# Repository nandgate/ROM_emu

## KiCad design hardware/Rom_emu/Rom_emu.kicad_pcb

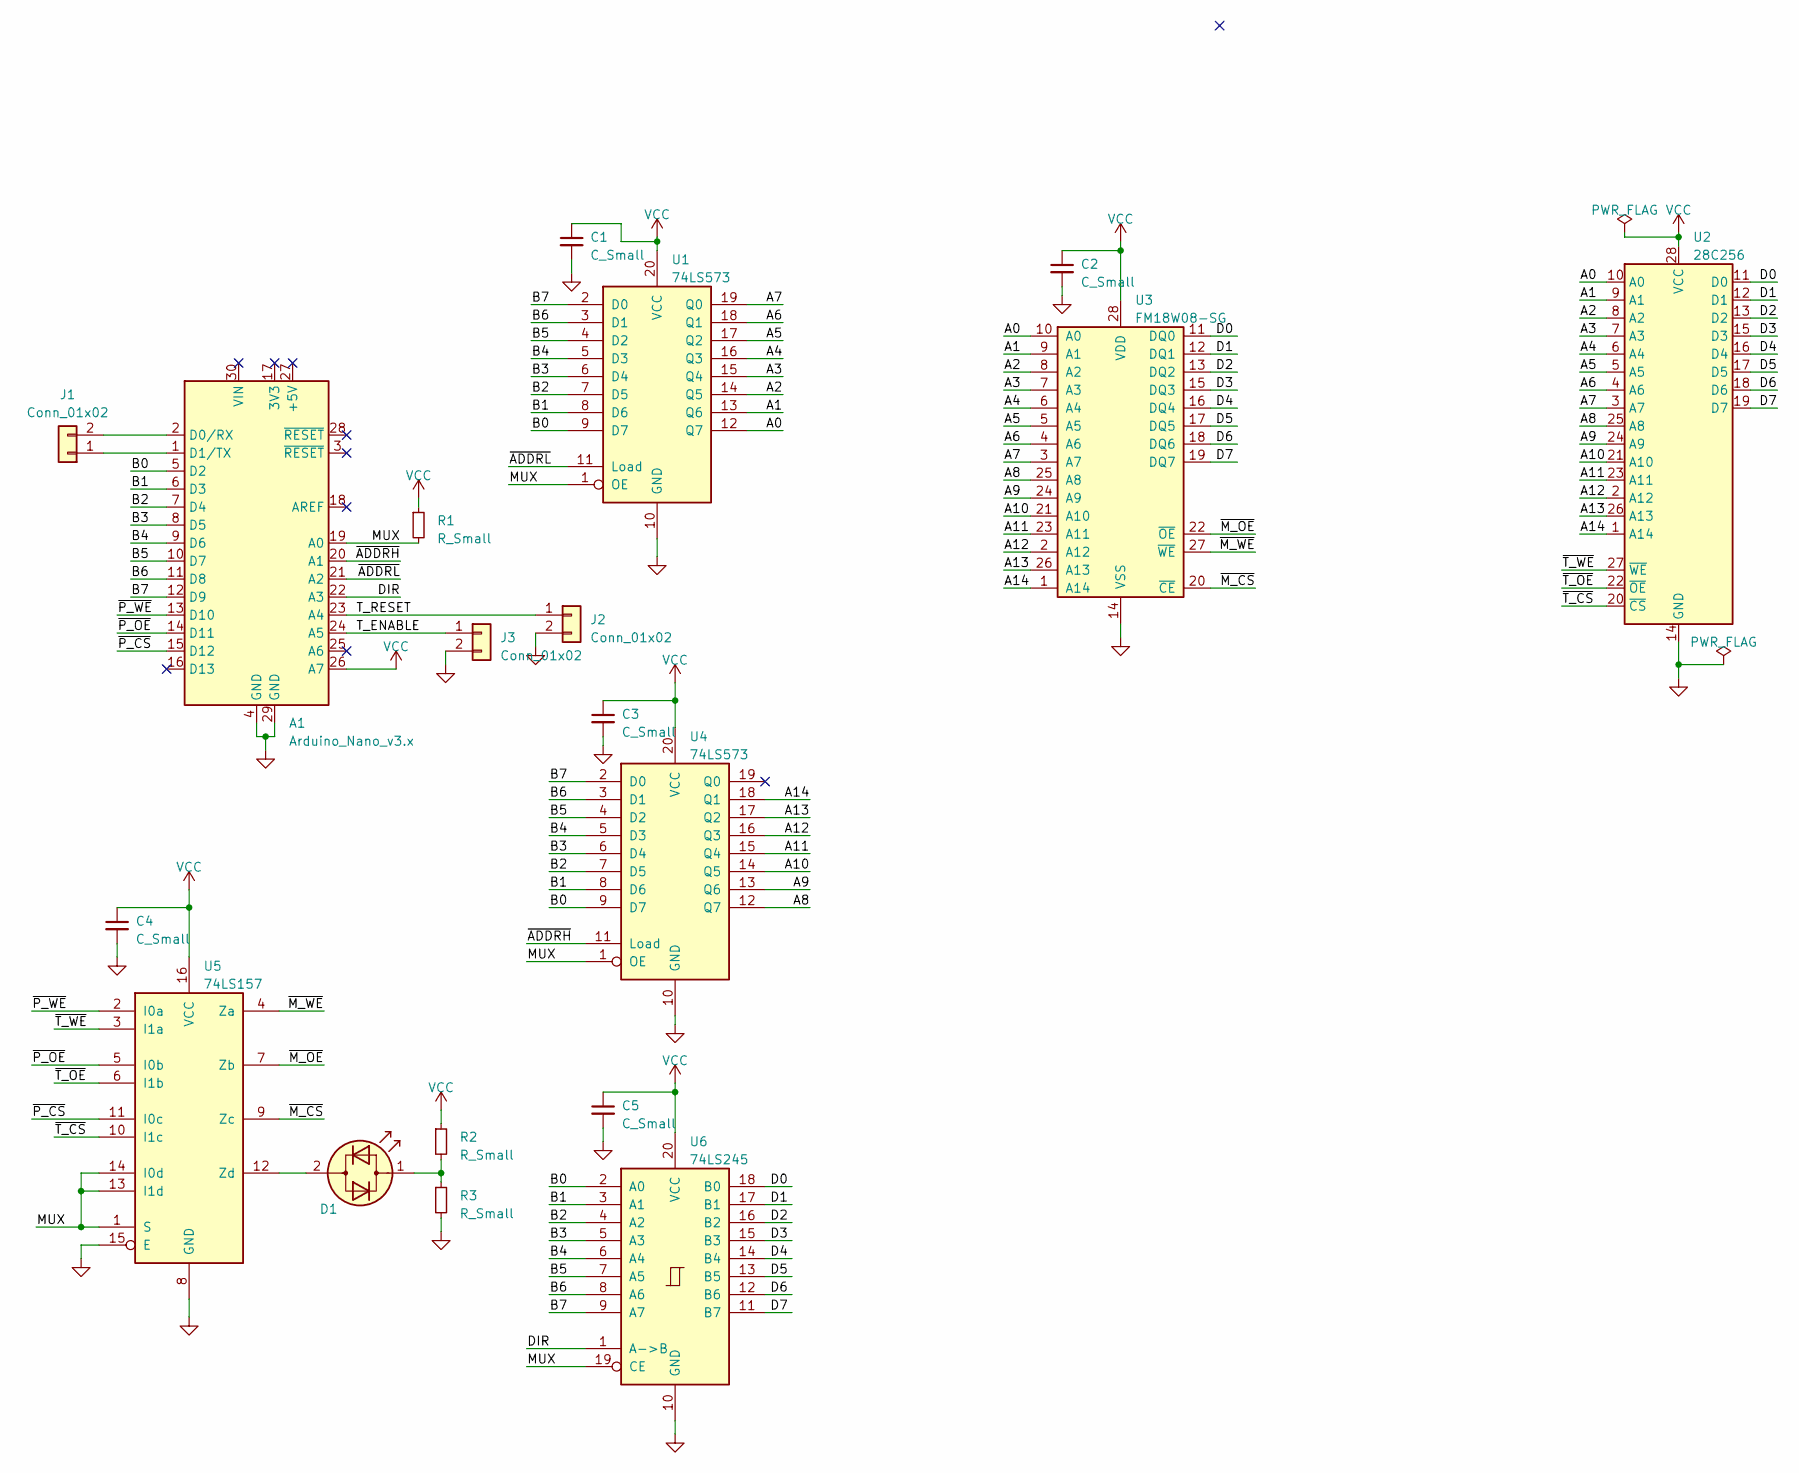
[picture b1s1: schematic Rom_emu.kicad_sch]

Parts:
A1: Arduino_Nano_v3.x; Arduino_Nano
C1, C2, C3, C4, C5: C_Small; C_Rect_L7.2mm_W3.0mm_P5.00mm_FKS2_FKP2_MKS2_MKP2
D1: LED_Dual_Bidirectional; LED_D5.0mm_FlatTop
J1, J2, J3: Conn_01x02; PinHeader_1x02_P2.54mm_Vertical
R1, R2, R3: R_Small; R_Axial_DIN0207_L6.3mm_D2.5mm_P10.16mm_Horizontal
U1, U4: 74LS573; DIP-20_W7.62mm
U2: 28C256; DIP-28_W7.62mm
U3: FM18W08-SG; SOIC-28W_7.5x17.9mm_P1.27mm
U5: 74LS157; DIP-16_W7.62mm
U6: 74LS245; DIP-20_W7.62mm

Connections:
/A0: U1.12 (Q7), U2.10 (A0), U3.10 (A0)
/A1: U1.13 (Q6), U2.9 (A1), U3.9 (A1)
/A2: U1.14 (Q5), U2.8 (A2), U3.8 (A2)
/A3: U1.15 (Q4), U2.7 (A3), U3.7 (A3)
/A4: U1.16 (Q3), U2.6 (A4), U3.6 (A4)
/A5: U1.17 (Q2), U2.5 (A5), U3.5 (A5)
/A6: U1.18 (Q1), U2.4 (A6), U3.4 (A6)
/A7: U1.19 (Q0), U2.3 (A7), U3.3 (A7)
/A8: U2.25 (A8), U3.25 (A8), U4.12 (Q7)
/A9: U2.24 (A9), U3.24 (A9), U4.13 (Q6)
/A10: U2.21 (A10), U3.21 (A10), U4.14 (Q5)
/A11: U2.23 (A11), U3.23 (A11), U4.15 (Q4)
/A12: U2.2 (A12), U3.2 (A12), U4.16 (Q3)
/A13: U2.26 (A13), U3.26 (A13), U4.17 (Q2)
/A14: U2.1 (A14), U3.1 (A14), U4.18 (Q1)
/B0: A1.5 (D2), U1.9 (D7), U4.9 (D7), U6.2 (A0)
/B1: A1.6 (D3), U1.8 (D6), U4.8 (D6), U6.3 (A1)
/B2: A1.7 (D4), U1.7 (D5), U4.7 (D5), U6.4 (A2)
/B3: A1.8 (D5), U1.6 (D4), U4.6 (D4), U6.5 (A3)
/B4: A1.9 (D6), U1.5 (D3), U4.5 (D3), U6.6 (A4)
/B5: A1.10 (D7), U1.4 (D2), U4.4 (D2), U6.7 (A5)
/B6: A1.11 (D8), U1.3 (D1), U4.3 (D1), U6.8 (A6)
/B7: A1.12 (D9), U1.2 (D0), U4.2 (D0), U6.9 (A7)
/D0: U2.11 (D0), U3.11 (DQ0), U6.18 (B0)
/D1: U2.12 (D1), U3.12 (DQ1), U6.17 (B1)
/D2: U2.13 (D2), U3.13 (DQ2), U6.16 (B2)
/D3: U2.15 (D3), U3.15 (DQ3), U6.15 (B3)
/D4: U2.16 (D4), U3.16 (DQ4), U6.14 (B4)
/D5: U2.17 (D5), U3.17 (DQ5), U6.13 (B5)
/D6: U2.18 (D6), U3.18 (DQ6), U6.12 (B6)
/D7: U2.19 (D7), U3.19 (DQ7), U6.11 (B7)
/DIR: A1.22 (A3), U6.1 (A->B)
/MUX: A1.19 (A0), R1.2, U1.1 (OE), U4.1 (OE), U5.1 (S), U5.13 (I1d), U5.14 (I0d), U6.19 (CE)
/T_ENABLE: A1.24 (A5), J3.1
/T_RESET: A1.23 (A4), J2.1
/~ADDRH: A1.20 (A1), U4.11 (Load)
/~ADDRL: A1.21 (A2), U1.11 (Load)
/~M_CS: U3.20 (~CE), U5.9 (Zc)
/~M_OE: U3.22 (~OE), U5.7 (Zb)
/~M_WE: U3.27 (~WE), U5.4 (Za)
/~P_CS: A1.15 (D12), U5.11 (I0c)
/~P_OE: A1.14 (D11), U5.5 (I0b)
/~P_WE: A1.13 (D10), U5.2 (I0a)
/~T_CS: U2.20 (~CS), U5.10 (I1c)
/~T_OE: U2.22 (~OE), U5.6 (I1b)
/~T_WE: U2.27 (~WE), U5.3 (I1a)
GND: A1.4 (GND), A1.29 (GND), C1.2, C2.2, C3.2, C4.2, C5.2, J2.2, J3.2, R3.2, U1.10 (GND), U2.14 (GND), U3.14 (VSS), U4.10 (GND), U5.8 (GND), U5.15 (E), U6.10 (GND)
unnamed: A1.2 (D0/RX), J1.2
unnamed: A1.1 (D1/TX), J1.1
unnamed: D1.2 (AK), U5.12 (Zd)
unnamed: D1.1 (KA), R2.2, R3.1
VCC: A1.26 (A7), C1.1, C2.1, C3.1, C4.1, C5.1, R1.1, R2.1, U1.20 (VCC), U2.28 (VCC), U3.28 (VDD), U4.20 (VCC), U5.16 (VCC), U6.20 (VCC)

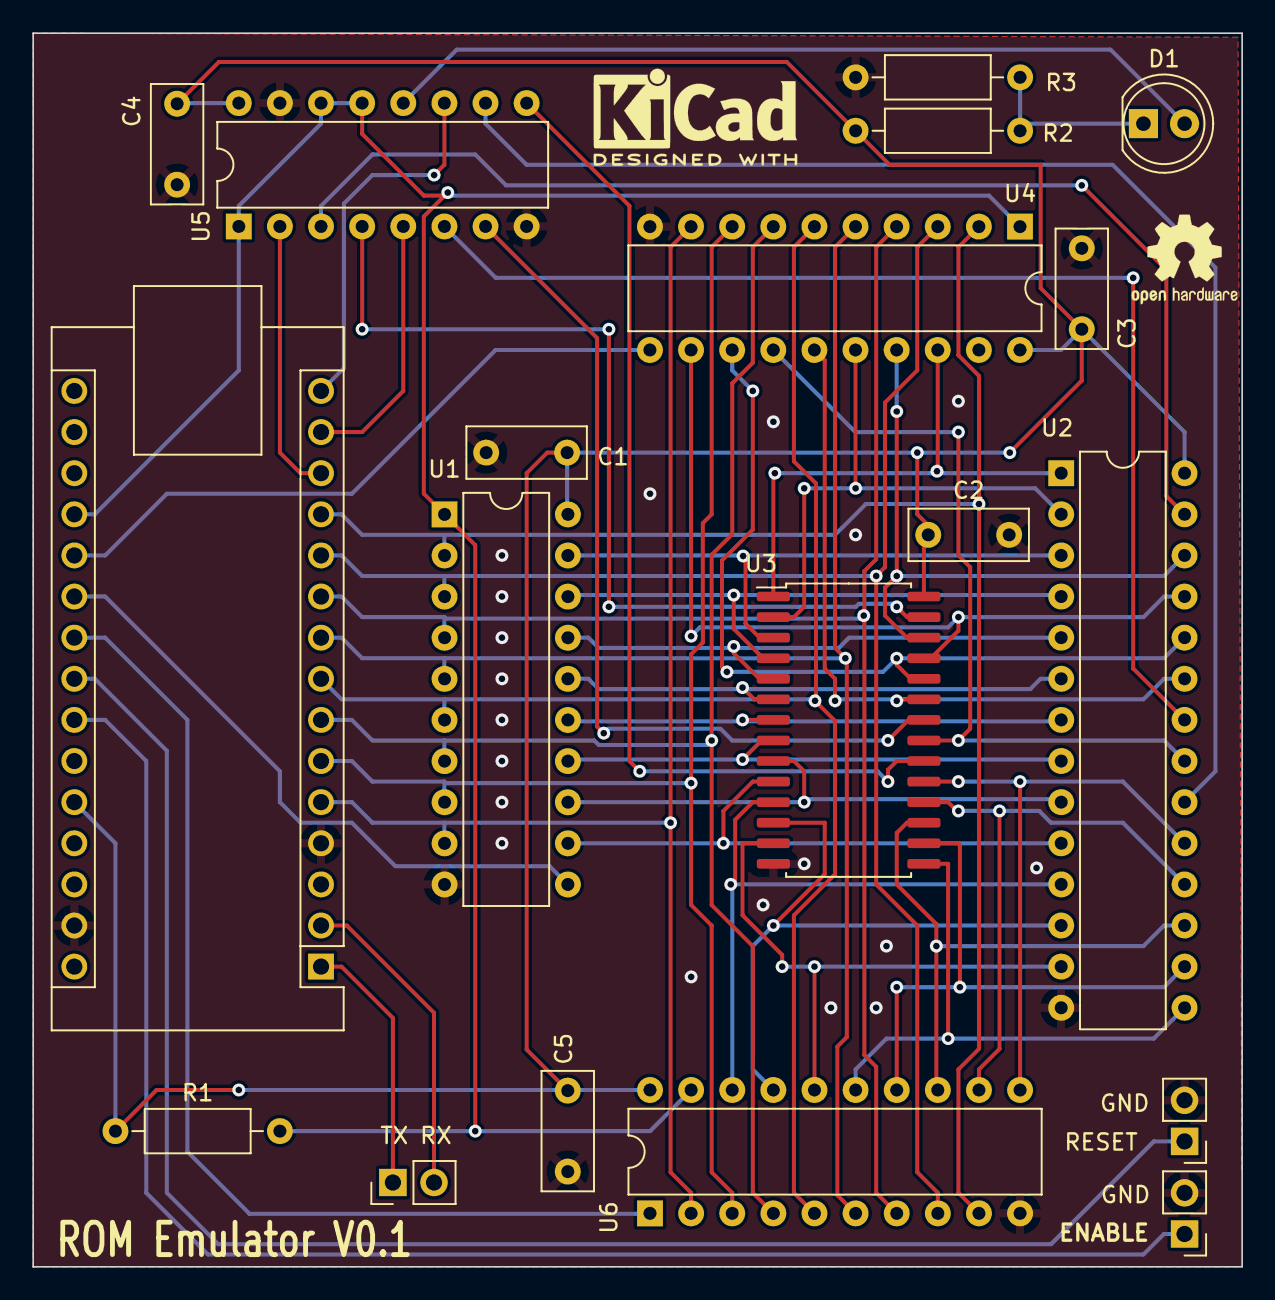
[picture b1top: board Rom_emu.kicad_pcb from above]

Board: 2 copper layers, 74.7 x 76.2 mm, 19 parts (0 on the bottom side), 52 nets.

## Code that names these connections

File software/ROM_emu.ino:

uint16_t addr;
uint16_t user;

#define B0      2
#define B1      3
#define B2      4
#define B3      5
#define B4      6
#define B5      7
#define B6      8
#define B7      9
#define P_WE    10
#define P_OE    11
#define P_CS    12
#define MUX     14
#define ADDRH   15
#define ADDRL   16
#define DIR     17
#define T_RESET 18
#define T_EN    19
#define PWR     7

void Init_HW(void) {
  pinMode(MUX, OUTPUT);     digitalWrite(MUX, HIGH);
  pinMode(P_WE, OUTPUT);    digitalWrite(P_WE, HIGH);
  pinMode(P_OE, OUTPUT);    digitalWrite(P_OE, HIGH);
  pinMode(P_CS, OUTPUT);    digitalWrite(P_CS, HIGH);
  pinMode(ADDRH, OUTPUT);   digitalWrite(ADDRH, HIGH);
  pinMode(ADDRL, OUTPUT);   digitalWrite(ADDRL, HIGH);
  pinMode(DIR, OUTPUT);     digitalWrite(DIR, LOW);
  pinMode(T_RESET, OUTPUT); digitalWrite(T_RESET, HIGH);
  pinMode(T_EN, OUTPUT);    digitalWrite(T_EN, HIGH);

}

uint8_t BusIn(void) {
  uint8_t value = 0;

  pinMode(B0, INPUT);
  pinMode(B1, INPUT);
  pinMode(B2, INPUT);
  pinMode(B3, INPUT);
  pinMode(B4, INPUT);
  pinMode(B5, INPUT);
  pinMode(B6, INPUT);
  pinMode(B7, INPUT);

  value |= (digitalRead(B0) == HIGH) ? 0x01 : 0;
  value |= (digitalRead(B1) == HIGH) ? 0x02 : 0;
  value |= (digitalRead(B2) == HIGH) ? 0x04 : 0;
  value |= (digitalRead(B3) == HIGH) ? 0x08 : 0;
  value |= (digitalRead(B4) == HIGH) ? 0x10 : 0;
  value |= (digitalRead(B5) == HIGH) ? 0x20 : 0;
  value |= (digitalRead(B6) == HIGH) ? 0x40 : 0;
  value |= (digitalRead(B7) == HIGH) ? 0x80 : 0;

  return value;
}

void BusOut(uint8_t value) {
  pinMode(B0, OUTPUT);
  pinMode(B1, OUTPUT);
  pinMode(B2, OUTPUT);
  pinMode(B3, OUTPUT);
  pinMode(B4, OUTPUT);
  pinMode(B5, OUTPUT);
  pinMode(B6, OUTPUT);
  pinMode(B7, OUTPUT);

  digitalWrite(B0, (value & 0x01) ? HIGH : LOW);
  digitalWrite(B1, (value & 0x02) ? HIGH : LOW);
  digitalWrite(B2, (value & 0x04) ? HIGH : LOW);
  digitalWrite(B3, (value & 0x08) ? HIGH : LOW);
  digitalWrite(B4, (value & 0x10) ? HIGH : LOW);
  digitalWrite(B5, (value & 0x20) ? HIGH : LOW);
  digitalWrite(B6, (value & 0x40) ? HIGH : LOW);
  digitalWrite(B7, (value & 0x80) ? HIGH : LOW);
}

void Strobe(uint8_t pin) {
  digitalWrite(pin, LOW);
  digitalWrite(pin, HIGH);
}

uint8_t Read(uint16_t address) {
  uint8_t data;

  Serial.print("RD");
  Serial.println(address, HEX);

  BusOut(addr >> 8);
  Strobe(ADDRH);
  BusOut(addr & 0xFF);
  Strobe(ADDRL);

  digitalWrite(DIR, LOW);
  digitalWrite(P_CS, LOW);
  digitalWrite(P_OE, LOW);
  data= BusIn();
  digitalWrite(P_OE, HIGH);
  digitalWrite(P_CS, HIGH);
  
  return data;
}

void Write(uint8_t address, uint8_t data) {
  Serial.print("WR");
  Serial.println(address, HEX);

  BusOut(addr >> 8);
  Strobe(ADDRH);
  BusOut(addr & 0xFF);
  Strobe(ADDRL);

  digitalWrite(DIR, HIGH);
  digitalWrite(P_CS, LOW);
  digitalWrite(P_WE, LOW);
  BusOut(data);
  digitalWrite(P_WE, HIGH);
  digitalWrite(P_CS, HIGH);
  digitalWrite(DIR, LOW);
}

void ShowInfo(void) {
  Serial.write("\nRom_emu,0.1\n");
}

void HexDigit(int ch) {
  user <<= 4;

  if (isDigit(ch)) {
    user |= (ch-'0');
  }
  else {
    ch = toLowerCase(ch);
    user |= ch-'a' + 10;
  }
}

bool DoCmd(int cmd) {
  if(isHexadecimalDigit(cmd)) {
    HexDigit(cmd);
    return false;
  } 
  else switch(cmd) {
    case '\r':
      return false;;
    case '?':
      ShowInfo();
      break;
    case '\n':
      Write(addr++, user);
      break;      
    case '+':
      addr++;
      break;
    case '-':
      addr--;
      break;
    case ' ':
      addr = user;
      break;
  }
  return true;
}

void prompt(void) {
  Serial.print('\n');
  Serial.print(addr, HEX);
  Serial.print(": ");
  Serial.print(Read(addr), HEX);
  Serial.write('>');
}

void setup() {
  Serial.begin(19200);
  Init_HW();
  pinMode(LED_BUILTIN, OUTPUT);
  ShowInfo();
  addr = 0;
  user = 0;
  prompt();
}

void loop() {
  if(Serial.available() > 0) {
    int ch = Serial.read();
    if(DoCmd(ch)) {
      prompt();
    }
  }
}

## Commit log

2023-03-08 First pass on software, incomplete.
